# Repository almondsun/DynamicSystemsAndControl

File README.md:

# Sistemas Dinámicos y Control

Coursework and final Buck-converter project at Universidad Nacional de Colombia, Sede Manizales.

## Final project

- [Project documentation](project/README.md)
- [Four IEEE deliverable reports](project/reports/final/)
- [Hardware appendix: 3D views, schematics and wiring](project/pcb/release/hardware-appendix.pdf)
- [PCB design and build instructions](project/pcb/README.md)
- [STM32 firmware](project/firmware/README.md)
- [Requirements audit and next steps](project/pcb/docs/requirements-audit.md)
- [Buck SMD/JLCPCB audit: inventory, passive requirements and open issues](project/pcb/audit/README.md)
- [Team review package](project/pcb/release/buck-team-review.zip)

The design targets 12 V input, 6 V nominal output and 10 kHz PWM. Reports distinguish numerical simulations and CAD checks from experimental evidence. Component qualification, prototype assembly and physical testing remain pending; PCB fabrication is on hold.

## Repository contents

- `classroom/`: assignment and course reference material.
- `simulations/`: MATLAB and Simulink coursework.
- `project/`: final-project sources, reports, compact numerical results, PCB and firmware.
- `tools/` and `docs/`: validation helpers and MATLAB setup documentation.

Local downloaded toolchains, full raw validation runs and caches under `artifacts/` are excluded from Git. Follow the project documentation for build dependencies and reproducibility limits. Course materials and third-party assets retain their respective rights; KiCad model licensing is included in `project/pcb/models/`.

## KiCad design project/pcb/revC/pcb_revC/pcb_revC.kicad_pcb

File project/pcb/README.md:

# Buck: PCB y controlador STM32 — revisión A

**Paquete de ingeniería para revisión. Fabricación retenida hasta completar
la calificación de componentes y el prototipo soldado.** No se ha comprado,
fabricado, ensamblado ni probado físicamente esta tarjeta.

El diseño original conserva 12 V, 660 µH, 20 µF, 6 Ω y PWM de 10 kHz del
proyecto de Sistemas Dinámicos y Control. Emplea dos inductores de 330 µH en
serie, IR2110, MOSFET IRFZ44N, rectificación 1N5822 y una Blue Pill externa.
El controlador PI conserva la interfaz existente `buck_update` en voltios y
la salida invertida **d′ = 1 − d**. La protección por corriente y tensión
es independiente del programa del STM32.

## Archivos para compartir con el equipo

- [Auditoría SMD/JLCPCB e índice de documentación actual](audit/README.md): inventario de 57 referencias, requisitos calculados de los 35 pasivos y selección comercial pendiente.
- [Bloqueos antes de cambiar el circuito o fabricar](audit/open_issues.md) y [comportamiento esperado y pruebas](audit/expected_behavior.md). Los resultados de revisión A que siguen abajo son históricos; no constituyen una validación de los nuevos candidatos SMD.
- [Organización de documentos y bibliotecas descargadas](audit/organization_by_type.md) y [uso del organizador local](docs/vendor-assets-organizer.md). Las descargas originales y bibliotecas comerciales permanecen fuera de Git.

- [Anexo visual de hardware](release/hardware-appendix.pdf): 3D, plano, conexiones y esquemas completos.
- [Cuatro informes IEEE actualizados](../reports/final/) y [auditoría de requisitos](docs/requirements-audit.md).
- [Vista 3D isométrica](release/report-assets/pcb-3d.png) y [superior](release/report-assets/pcb-top.png). Son vistas CAD; geometría de inductores y referencias de capacitores pendientes de calificación.
- [Paquete ZIP completo](release/buck-team-review.zip) y [resumen para el equipo](TEAM_OVERVIEW.md).
- [Esquemático PDF](release/schematic.pdf) y [proyecto KiCad](buck.kicad_pro).
- [Vista frontal](release/board-front.png), [vista posterior](release/board-back.png)
  y [plano de montaje](release/assembly.pdf).
- [BOM de la placa](bom.csv) y [lista de compra con reservas](purchasing.csv).
- [Presupuesto y proveedores](docs/purchasing.md).
- [Montaje, conexiones y ensayos](docs/assembly-and-tests.md).
- [Firmware y programación](../firmware/README.md).
- [Resultados de validación y límites](VALIDATION.md).
- [Archivos de fabricación para revisión](release/fabrication-review/).

Los Gerbers son una exportación de revisión, **no una autorización para
encargar placas**. La geometría de L1/L2 es provisional: cuerpo máximo
25 mm, separación de terminales 10 mm, agujero 1.3 mm. Una bobina comercial
rotulada «330 µH, 5 A» no acredita esta geometría ni su corriente de saturación.
También deben cerrarse referencias exactas de los capacitores antes del pedido.

## Construcción y reproducción

Para actualizar las ilustraciones con las herramientas locales: `bash project/pcb/tools/render_review.sh`.
Esto adjunta modelos locales al PCB existente; no regenera ni enruta la placa. Tras ejecutar `generate.py`, repetir la importación de ruta y luego este paso de modelos. Ejecutar `export_review.sh` para comprobar ERC/DRC/paridad.
Los modelos estándar conservan su licencia oficial en `models/LICENSE-KiCad.md`; `models/manifest.json` registra procedencia y SHA-256. Las envolventes de inductores se generan en `prepare_3d.py` y no son modelos de fabricante.

Los informes se reconstruyen con `project/python/build_reports.py` y los resultados completos guardados, según el README del proyecto. La fuente del anexo es `docs/hardware-appendix.tex`; compilar desde `release/` para resolver los PDF y figuras incluidos. Los CSV compactos del ZIP permiten revisar resultados y ejecutar pruebas; regenerar las gráficas de rizado requiere las ondas completas de la ejecución original.

KiCad 10.0.6, bibliotecas estándar de KiCad y Python `pcbnew`; GCC ARM para
STM32. Las bibliotecas propias están dentro de esta carpeta. No se necesita
una licencia comercial de CAD. El STM32 y su programador no están integrados
en la placa, por lo que pueden reemplazarse sin rehacerla.

`tools/design.py` contiene la conectividad, numeración de pines y colocación.
`tools/generate.py` genera los archivos editables y el DSN. **Regenerar reemplaza
los archivos CAD generados**: conservar por separado cualquier revisión manual.
`tools/finish_board.py` importa la sesión de Freerouting y añade el plano GND.
Las comprobaciones finales y sus comandos están en `VALIDATION.md`.

El circuito de `simulation/` es una estimación con pérdidas y el código real
del controlador; no reemplaza el modelo Simulink ni los resultados originales.
Los informes de las entregas 2 y 4 siguen pendientes de evidencia experimental.

## Especificación de fabricación propuesta

99 × 99 mm; 2 capas; FR-4 de 1.6 mm; cobre de 1 oz; máscara verde;
acabado HASL sin plomo o estándar según el presupuesto; cinco placas desnudas;
sin montaje, stencil ni opciones premium. Señales de 0.30 mm, conexiones de
potencia de 0.60 mm y plano GND posterior; separación de ruteo 0.25 mm;
vías de 1.20/0.60 mm. Verificar calentamiento y caídas de tensión en banco:
estas dimensiones no sustituyen la validación térmica.
La salida GND de baja corriente de U6 incluye un escape local de 0.36 mm.
Su salida ISENSE incluye dos segmentos locales de 0.225 mm entre pads SOT23.

No hay orificios para chasis. Sujetar la placa por sus bordes con un soporte
aislante; los inductores pesados necesitan fijación aislante que no obstruya
la refrigeración. Nunca apoyar la cara inferior sobre una superficie metálica.

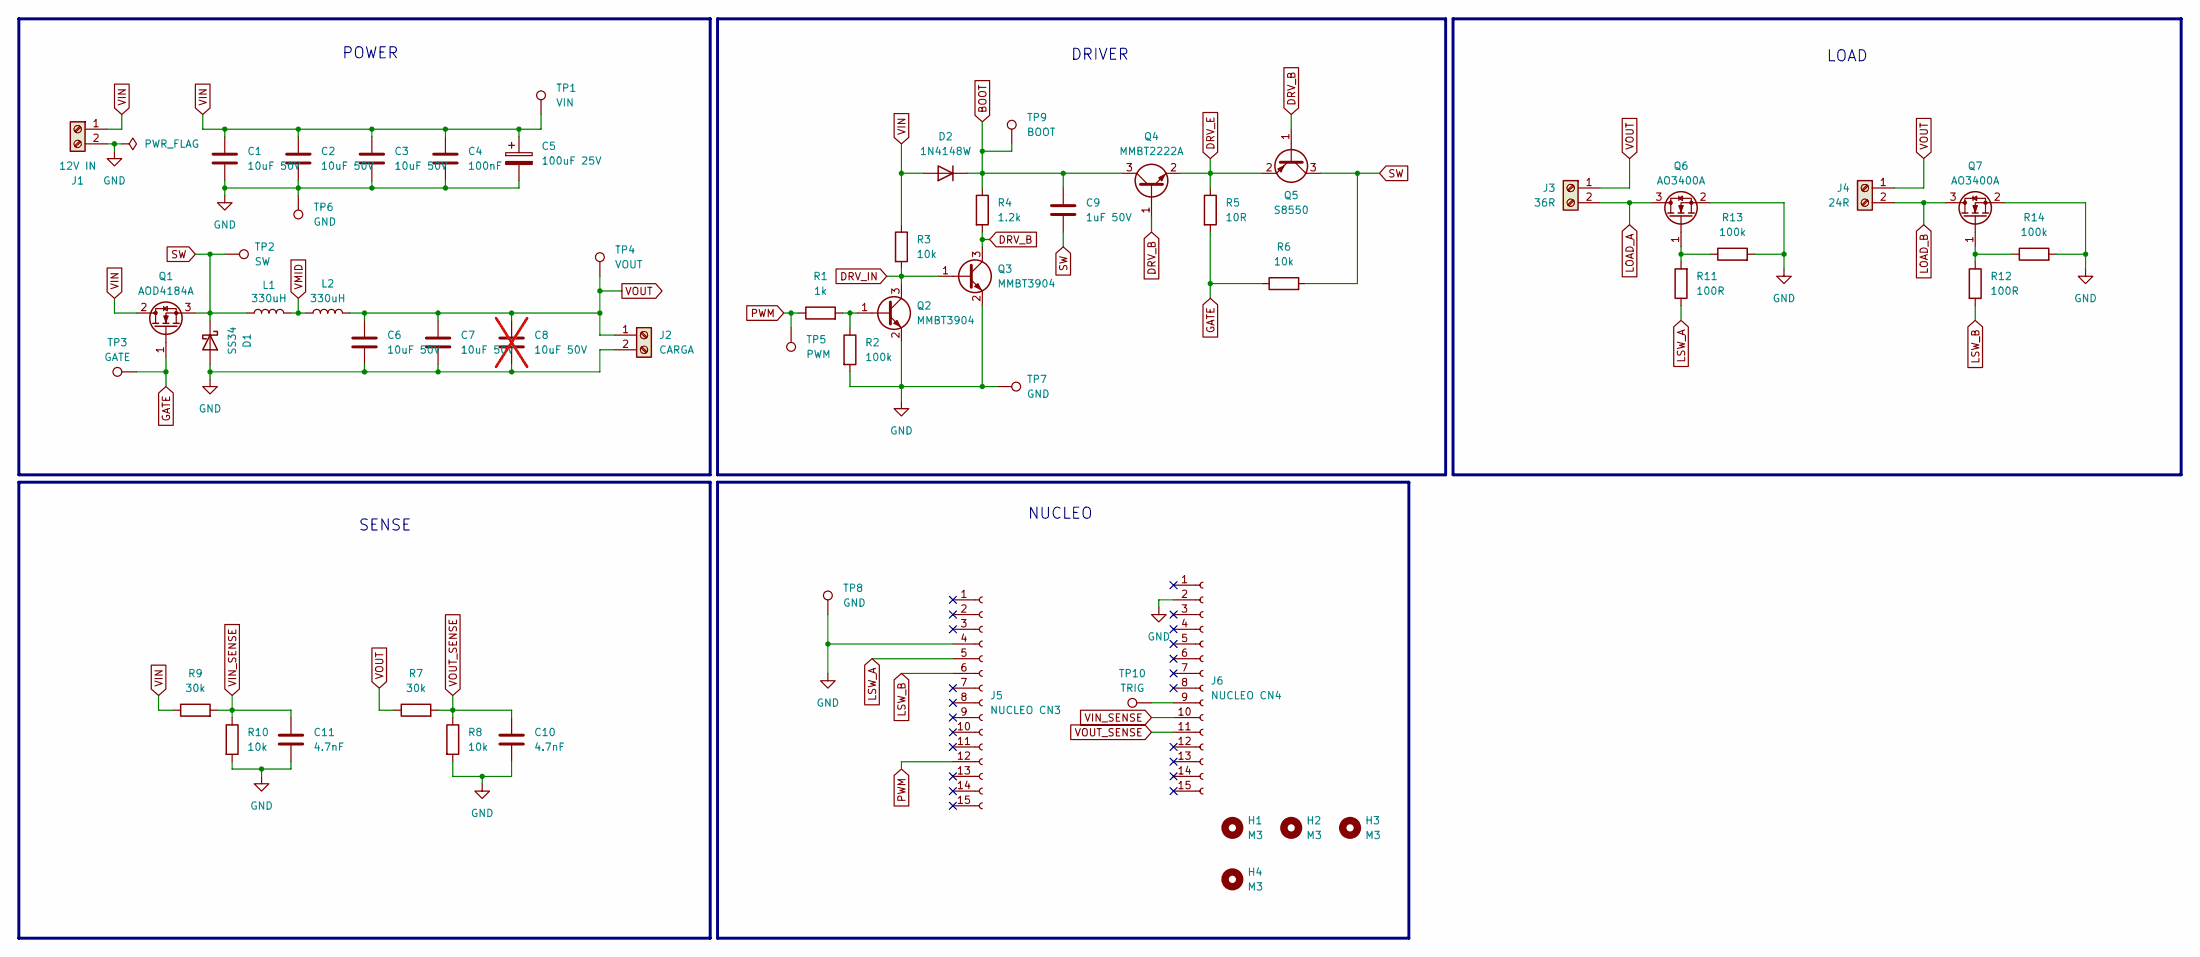
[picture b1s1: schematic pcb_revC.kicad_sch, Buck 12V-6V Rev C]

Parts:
C1, C2, C3, C6, C7: 10uF 50V; C_1206_3216Metric; LCSC C13585
C4: 100nF; C_0603_1608Metric; LCSC C14663
C5: 100uF 25V; CP_Radial_D6.3mm_P2.50mm
C8: 10uF 50V; C_1206_3216Metric; LCSC C13585; not fitted
C9: 1uF 50V; C_0805_2012Metric; LCSC C28323
C10, C11: 4.7nF; C_0603_1608Metric; LCSC C53987
D1: SS34; D_SMA; LCSC C8678
D2: 1N4148W; D_SOD-123; LCSC C81598
H1, H2, H3, H4: M3; MountingHole_3.2mm_M3
J1: 12V IN; TerminalBlock_Phoenix_MKDS-1,5-2_1x02_P5.00mm_Horizontal
J2: CARGA; TerminalBlock_Phoenix_MKDS-1,5-2_1x02_P5.00mm_Horizontal
J3: 36R; TerminalBlock_Phoenix_MKDS-1,5-2_1x02_P5.00mm_Horizontal
J4: 24R; TerminalBlock_Phoenix_MKDS-1,5-2_1x02_P5.00mm_Horizontal
J5: NUCLEO CN3; PinSocket_1x15_P2.54mm_Vertical
J6: NUCLEO CN4; PinSocket_1x15_P2.54mm_Vertical
L1, L2: 330uH; L_Bourns_SRR1280; LCSC C2041412
Q1: AOD4184A; TO-252-2; LCSC C99124
Q2, Q3: MMBT3904; SOT-23; LCSC C20526
Q4: MMBT2222A; SOT-23; LCSC C8512
Q5: S8550; SOT-23; LCSC C105432
Q6, Q7: AO3400A; SOT-23; LCSC C20917
R1: 1k; R_0603_1608Metric; LCSC C21190
R2, R13, R14: 100k; R_0603_1608Metric; LCSC C25803
R3, R6, R8, R10: 10k; R_0603_1608Metric; LCSC C25804
R4: 1.2k; R_0805_2012Metric; LCSC C17379
R5: 10R; R_0603_1608Metric; LCSC C22859
R7, R9: 30k; R_0603_1608Metric; LCSC C22984
R11, R12: 100R; R_0603_1608Metric; LCSC C22775
TP1: VIN; TestPoint_THTPad_D2.0mm_Drill1.0mm
TP2: SW; TestPoint_THTPad_D2.0mm_Drill1.0mm
TP3: GATE; TestPoint_THTPad_D2.0mm_Drill1.0mm
TP4: VOUT; TestPoint_THTPad_D2.0mm_Drill1.0mm
TP5: PWM; TestPoint_THTPad_D2.0mm_Drill1.0mm
TP6, TP7, TP8: GND; TestPoint_THTPad_D2.0mm_Drill1.0mm
TP9: BOOT; TestPoint_THTPad_D2.0mm_Drill1.0mm
TP10: TRIG; TestPoint_THTPad_D2.0mm_Drill1.0mm

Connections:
BOOT: C9.1, D2.1 (K), Q4.3 (C), R4.1, TP9.1 (1_1)
DRV_B: Q3.3 (C), Q4.1 (B), Q5.1 (B), R4.2
DRV_E: Q4.2 (E), Q5.2 (E), R5.1
DRV_IN: Q2.3 (C), Q3.1 (B), R3.2
GATE: Q1.1 (G), R5.2, R6.1, TP3.1 (1_1)
GND: C1.2, C2.2, C3.2, C4.2, C5.2, C6.2, C7.2, C8.2, C10.2, C11.2, D1.2 (A), J1.2, J2.2, J5.4, J6.2, Q2.2 (E), Q3.2 (E), Q6.2 (S), Q7.2 (S), R2.2, R8.2, R10.2, R13.2, R14.2, TP6.1 (1_1), TP7.1 (1_1), TP8.1 (1_1)
LOAD_A: J3.2, Q6.3 (D)
LOAD_B: J4.2, Q7.3 (D)
LSW_A: J5.5, R11.1
LSW_B: J5.6, R12.2
unnamed: J6.9, TP10.1 (1_1)
unnamed: Q2.1 (B), R1.2, R2.1
unnamed: Q6.1 (G), R11.2, R13.1
unnamed: Q7.1 (G), R12.1, R14.1
PWM: J5.12, R1.1, TP5.1 (1_1)
SW: C9.2, D1.1 (K), L1.2, Q1.3 (S), Q5.3 (C), R6.2, TP2.1 (1_1)
VIN: C1.1, C2.1, C3.1, C4.1, C5.1, D2.2 (A), J1.1, Q1.2 (D), R3.1, R9.1, TP1.1 (1_1)
VIN_SENSE: C11.1, J6.10, R9.2, R10.1
VMID: L1.1, L2.1
VOUT: C6.1, C7.1, C8.1, J2.1, J3.1, J4.1, L2.2, R7.1, TP4.1 (1_1)
VOUT_SENSE: C10.1, J6.11, R7.2, R8.1

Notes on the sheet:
DRIVER
POWER
SENSE
NUCLEO
LOAD

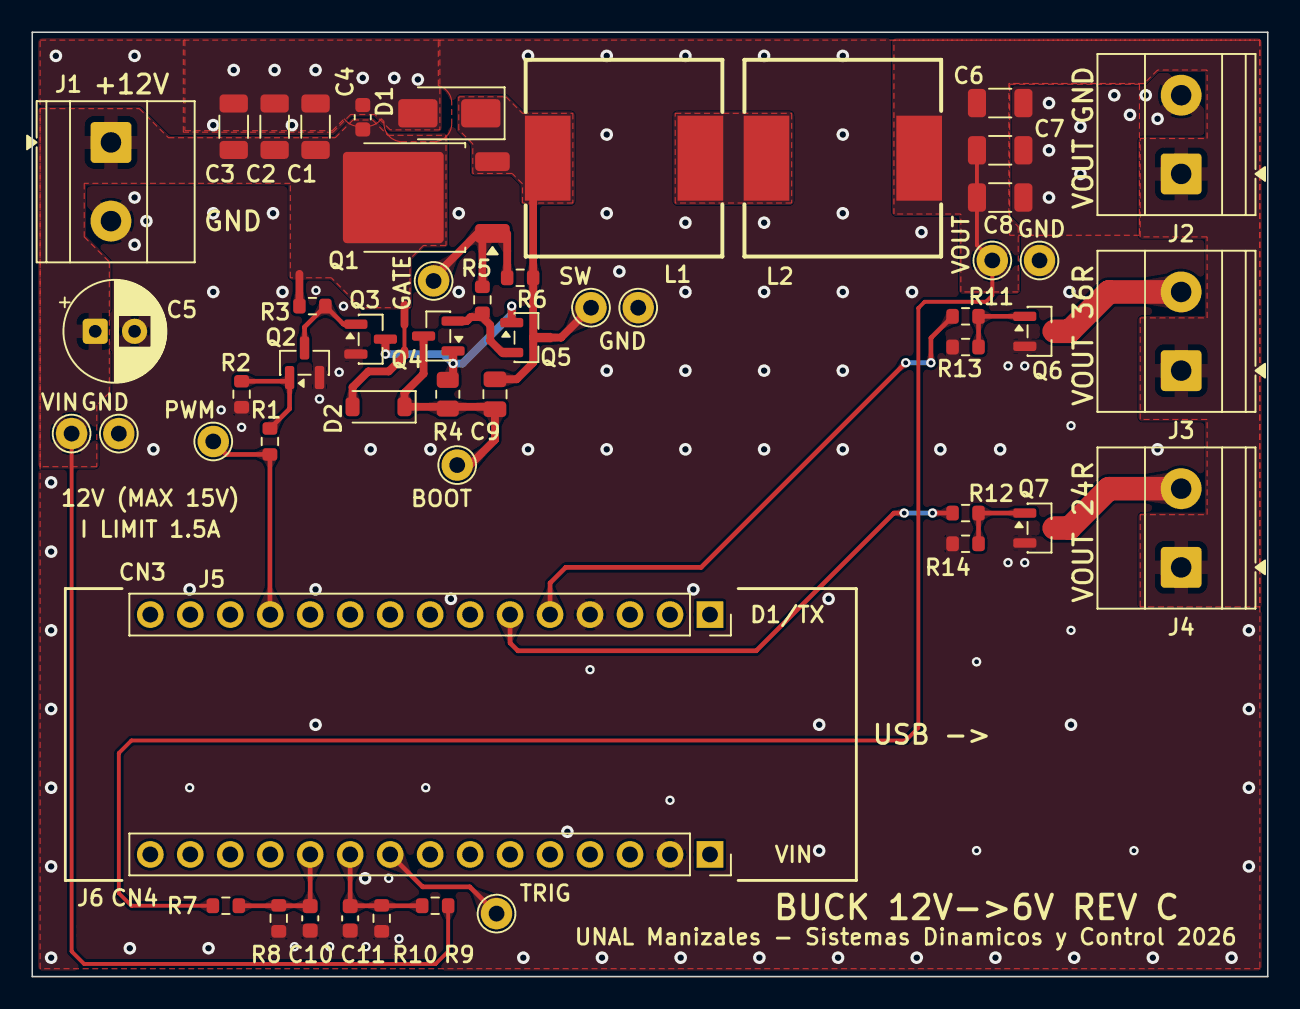
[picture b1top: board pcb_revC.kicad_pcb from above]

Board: 2 copper layers, 78.5 x 60.0 mm, 52 parts (0 on the bottom side), 21 nets.

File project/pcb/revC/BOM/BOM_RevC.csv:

Designator,Value,Package,LCSC,Library,Qty_per_board,Source,Notes
"L1,L2",SRR1280-331K 330uH 1.1A Isat1.4A DCR0.6R,SMD 12.5x12.5mm,C2041412,Extended,2,JLCPCB (reservados en My Parts Lib),En serie = 660uH; usar stock reservado
Q1,AOD4184A 40V 7mOhm,TO-252,C99124,Extended,1,JLCPCB,G=1 D=2/pestana S=3 - verificar datasheet
D1,SS34 40V 3A,SMA,C8678,Basic,1,JLCPCB,Catodo a SW
"C1,C2,C3,C6,C7",10uF 50V X5R,1206,C13585,Basic,5,JLCPCB,
C8,10uF 50V X5R,1206,C13585,Basic,0,JLCPCB,DNP - posicion de reserva
C4,100nF 50V X7R,0603,C14663,Basic,1,JLCPCB,Junto al drenador de Q1
C9,1uF 50V X7R,0805,C28323,Basic,1,JLCPCB,Bootstrap BOOT-SW
"C10,C11",4.7nF 50V X7R,0603,C53987,Basic,2,JLCPCB,Filtro ADC
"Q2,Q3",MMBT3904,SOT-23,C20526,Basic,2,JLCPCB,
Q4,MMBT2222A,SOT-23,C8512,Basic,1,JLCPCB,NPN del totem
Q5,S8550,SOT-23,C105432,Basic,1,JLCPCB,PNP del totem
"Q6,Q7",AO3400A,SOT-23,C20917,Basic,2,JLCPCB,Conmutacion de carga
D2,1N4148W,SOD-123,C81598,Basic,1,JLCPCB,Diodo de bootstrap
R1,1k 1%,0603,C21190,Basic,1,JLCPCB,
"R2,R13,R14",100k 1%,0603,C25803,Basic,3,JLCPCB,
"R3,R6,R8,R10",10k 1%,0603,C25804,Basic,4,JLCPCB,
R4,1.2k 1%,0805,C17379,Basic,1,JLCPCB,~44 mW promedio
R5,10R 1%,0603,C22859,Basic,1,JLCPCB,Resistencia de compuerta
"R7,R9",30k 1%,0603,C22984,Basic,2,JLCPCB,Divisores x0.25
"R11,R12",100R 1%,0603,C22775,Basic,2,JLCPCB,Compuerta de Q6/Q7
"J1,J2,J3,J4",Bornera 2P paso 5.0mm (KF301-5.0-2P),THT,,,4,Local,Paso 5.0 mm (huella Phoenix MKDS 5.00 mm) - no 5.08
"J5,J6",Header hembra 1x15 2.54mm,THT,,,2,Local,NUCLEO-L432KC CN3/CN4
C5,Electrolitico 100uF 25V o 35V radial 6.3mm paso 2.5mm 105C bajo ESR,THT,,,1,Local,Montar (soldar a mano). Rizado >= 0.3 A a 100 kHz. + = pad cuadrado (VIN)
"TP1-TP10",Test point pad 2.0mm / taladro 1.0mm,THT pad,,,10,Local,Pines macho 2.54 mm opcionales (VIN SW GATE VOUT PWM GND x3 BOOT TRIG)
"H1-H4",Agujero M3,NPTH 3.2mm,,,0,—,ELIMINADOS 2026-11-03 (sin agujeros M3; excluidos de la placa en el esquematico)
RCARGA_BASE,3.6R 10W x2 en serie (7.2R),Fuera de placa,,,2,Local,A J2
RCARGA_A,36R 5W,Fuera de placa,,,1,Local,A J3
RCARGA_B,24R 5W,Fuera de placa,,,1,Local,A J4

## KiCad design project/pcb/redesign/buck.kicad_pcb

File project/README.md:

# Proyecto final: convertidor Buck

Proyecto basado en `classroom/Descripcion Proyecto Buck.pdf`. Están desarrolladas
las entregas de simulación 1 y 3. Las entregas 2 y 4 incluyen metodología y
herramientas de análisis, pero requieren construir el convertidor y obtener
mediciones reales; no se presentan datos inventados.

## Documentos y modelo

La selección SMD para JLCPCB se documenta en la [auditoría de componentes del Buck](pcb/audit/README.md): inventario, requisitos eléctricos y térmicos de los 35 pasivos, candidatos comerciales y bloqueos. Es una revisión documental posterior al diseño original; no aprueba componentes ni fabricación y no recalifica los resultados históricos para SMD.

| Entrega | Archivo | Estado |
|---|---|---|
| 1. Modelo y simulación | [Informe PDF](reports/final/entrega_1.pdf) · [Fuente LaTeX](reports/final/entrega_1.tex) | Simulación completada |
| 2. Lazo abierto experimental | [Documento PDF](reports/final/entrega_2.pdf) · [Fuente LaTeX](reports/final/entrega_2.tex) | Ensayos físicos pendientes |
| 3. Diseño del PI | [Informe PDF](reports/final/entrega_3.pdf) · [Fuente LaTeX](reports/final/entrega_3.tex) | Simulación completada |
| 4. Controlador implementado | [Documento PDF](reports/final/entrega_4.pdf) · [Fuente LaTeX](reports/final/entrega_4.tex) | Integración y ensayos físicos pendientes |

- [Modelo Simulink](models/buck_control.slx): PI, saturación, anti-windup,
  driver inversor y planta promediada. Parámetros guardados en el workspace del modelo.
- [Circuito ngspice](circuit/buck.cir.in) y [descripción](circuit/README.md).
- [Implementación y protocolo de laboratorio](hardware/implementacion.md).
- [Núcleo C del controlador](hardware/buck_control.c): validado en computador;
  [adaptador STM32F103](firmware/README.md) compilable, con validación en computador;
  falta verificarlo en la tarjeta física.
- [PCB, lista de compra y protocolo de montaje](pcb/README.md): diseño KiCad
  de revisión; fabricación retenida hasta calificar componentes y prototipo.
- [Contrato de datos experimentales](data/README.md) y
  [analizador](python/analyze_experiment.py).
- [Registro de validación](VALIDATION.md).
- [Datos y evidencia numérica](results/README.md): CSV, MAT, JSON, netlists y logs.

## Parámetros y resultados

Vin=12 V, L=660 µH, C=20 µF, R=6 Ω, PWM=10 kHz. La figura del proyecto usa
660 µH; el valor 270 µH de `Ej_Buck.m` corresponde a otro ejemplo.

La entrada es **d′=1−d**. Aumentar d′ reduce la tensión. La planta incremental es

```text
Gd′(s) = −12 / (1.32e−8 s² + 1.10e−4 s + 1)
```

El PI actúa sobre el duty físico con Kp=0.0261655286 V⁻¹ y
Ki=78.4965859 (V·s)⁻¹; la salida lógica es d′=1−d. El diseño continuo tiene
102.07° de margen de fase y 4.83 ms de establecimiento nominal.

Los seis escenarios PWM/ngspice y los cuatro de Simulink pasan. En ngspice,
los cambios 6→7 V y 6→5 V se establecen en 4.95 ms (banda ±20 mV sobre medias
de periodo). Los cambios de R ±20% se establecen en 0.65 ms (banda ±0.12 V).
La diferencia por reducir el paso de ngspice a la mitad es 0.927 mV.

En lazo abierto, el circuito con pérdidas queda unos 0.30 V por debajo del
modelo ideal. El rizado es aproximadamente 0.28–0.29 V pico a pico. Los
semiconductores de ngspice son genéricos y DCR/ESR son supuestos explícitos;
estos resultados no certifican un montaje físico.

## Abrir y simular en MATLAB

Desde la raíz del repositorio:

```matlab
open_system('project/models/buck_control.slx')
in = Simulink.SimulationInput('buck_control');
in = in.setVariable('RefFinal',5,'Workspace','buck_control');
in = in.setVariable('RFinal',6,'Workspace','buck_control');
out = sim(in);
plot(out.buck_signals.Time, out.buck_signals.Data(:,1))
xlabel('Tiempo (s)'); ylabel('Tensión de salida (V)'); grid on
```

Para los otros escenarios elegir (RefFinal,RFinal): (7,6), (6,7.2), (6,4.8).
Las cuatro columnas registradas son tensión, corriente, d′ y referencia.
Condición inicial: 6 V y 1 A; evento a 10 ms; tiempo final 30 ms; ode45,
RelTol=1e-8, AbsTol=1e-10, MaxStep=10 µs. No se borra el workspace del usuario.

## Reproducir todo

Requisitos: MATLAB/Simulink/Control System Toolbox R2026a, ngspice 44.2,
Python 3.14 con [requirements.txt](python/requirements.txt), GCC y Tectonic
0.15.0 para los PDF LaTeX. No se necesitan Simscape, Simulink Test ni
Simulink Control Design. La reconstrucción estructural opcional utiliza el
toolkit oficial SATK, mediante `build_buck_model.m`; el modelo ya entregado
puede simularse sin SATK.

Con las herramientas disponibles en esta máquina:

```bash
BUCK_MATLAB=/home/mitin/MATLAB/R2026a/bin/matlab \
BUCK_PYTHON="$PWD/artifacts/buck-tools/venv/bin/python" \
BUCK_NGSPICE="$PWD/artifacts/buck-tools/ngspice/usr/bin/ngspice" \
bash project/run_project.sh
```

En otra máquina, instalar las dependencias de Python en un entorno virtual y
usar rutas propias o los ejecutables `matlab`, `python` y `ngspice` del PATH.
La distribución local de ngspice está extraída en `artifacts/buck-tools/`, sin
cambiar paquetes del sistema. Sus bibliotecas se seleccionan sólo para el
subproceso ngspice; no se cambian las bibliotecas de MATLAB.

El ejecutor crea una carpeta nueva bajo `artifacts/`, guarda CSV, MAT, JSON,
netlists por caso, formas de onda, logs, pruebas y PDF. Si se pasa una carpeta
ya existente, se detiene para evitar sobrescrituras. Ejemplo:
`bash project/run_project.sh artifacts/mi-nueva-ejecucion`.

## Completar las entregas físicas

Seguir `hardware/implementacion.md`: medir R/L/C y pérdidas; construir y
verificar la etapa de potencia y driver; elegir tarjeta; integrar ADC/PWM;
capturar dos ensayos de lazo abierto y cuatro de lazo cerrado con repeticiones.
Después, incorporar las mediciones y conclusiones a los documentos 2 y 4.
El analizador no convierte nominales de simulación en parámetros medidos.

## Reconstruir sólo los informes

Los cuatro PDF usan IEEEtran, ecuaciones LaTeX numeradas, CircuitikZ y gráficas
vectoriales PGFPlots. Las fuentes editables principales son `entrega_N.tex`;
los `.md` son compañeros con delimitadores matemáticos. Los autores aparecen
tanto en el documento como en los metadatos PDF. Las entregas 2 y 4 siguen
identificadas como metodologías con resultados experimentales pendientes.

El compilador local está en `artifacts/buck-tools/tectonic/tectonic`. Se puede
seleccionar otro con `BUCK_TECTONIC` o `--tectonic`. La primera compilación
necesita acceso a Internet para llenar la caché de paquetes de Tectonic.
El binario oficial utilizado es `tectonic-0.15.0-x86_64-unknown-linux-musl.tar.gz`,
de [la publicación 0.15.0](https://github.com/tectonic-typesetting/tectonic/releases/tag/tectonic%400.15.0).
SHA-256 del archivo descargado:
`dfb82876f2986862996e564fa507a9e576e0c1e3bee63c2c1bd677c2543e6407`.

```bash
artifacts/buck-tools/venv/bin/python -B project/python/build_reports.py \
  --matlab-results project/results/matlab \
  --analysis-results artifacts/buck-final-validation-02/simulation \
  --output artifacts/mis-informes-latex
```

La carpeta de salida debe ser nueva. Para reconstruir desde simulaciones se
requieren sus `waveform.txt`, además de JSON y CSV PWM, para obtener el detalle
instantáneo del rizado. Esto no vuelve a ejecutar MATLAB ni ngspice. Las fuentes
TeX entregadas también pueden compilarse directamente desde `reports/final/`:

```bash
../../../artifacts/buck-tools/tectonic/tectonic --keep-logs entrega_1.tex
```

El generador conserva los datos gráficos en `data/`, verifica coherencia de
parámetros y rechaza glifos faltantes, referencias indefinidas y desbordamientos.
La reducción de puntos retiene extremos por intervalo y extremos temporales;
las métricas proceden de resultados completos, sin recalcularlas sobre gráficos.
Validación de Python: `python -B -m unittest discover -s project/python -p 'test_*.py' -v`.

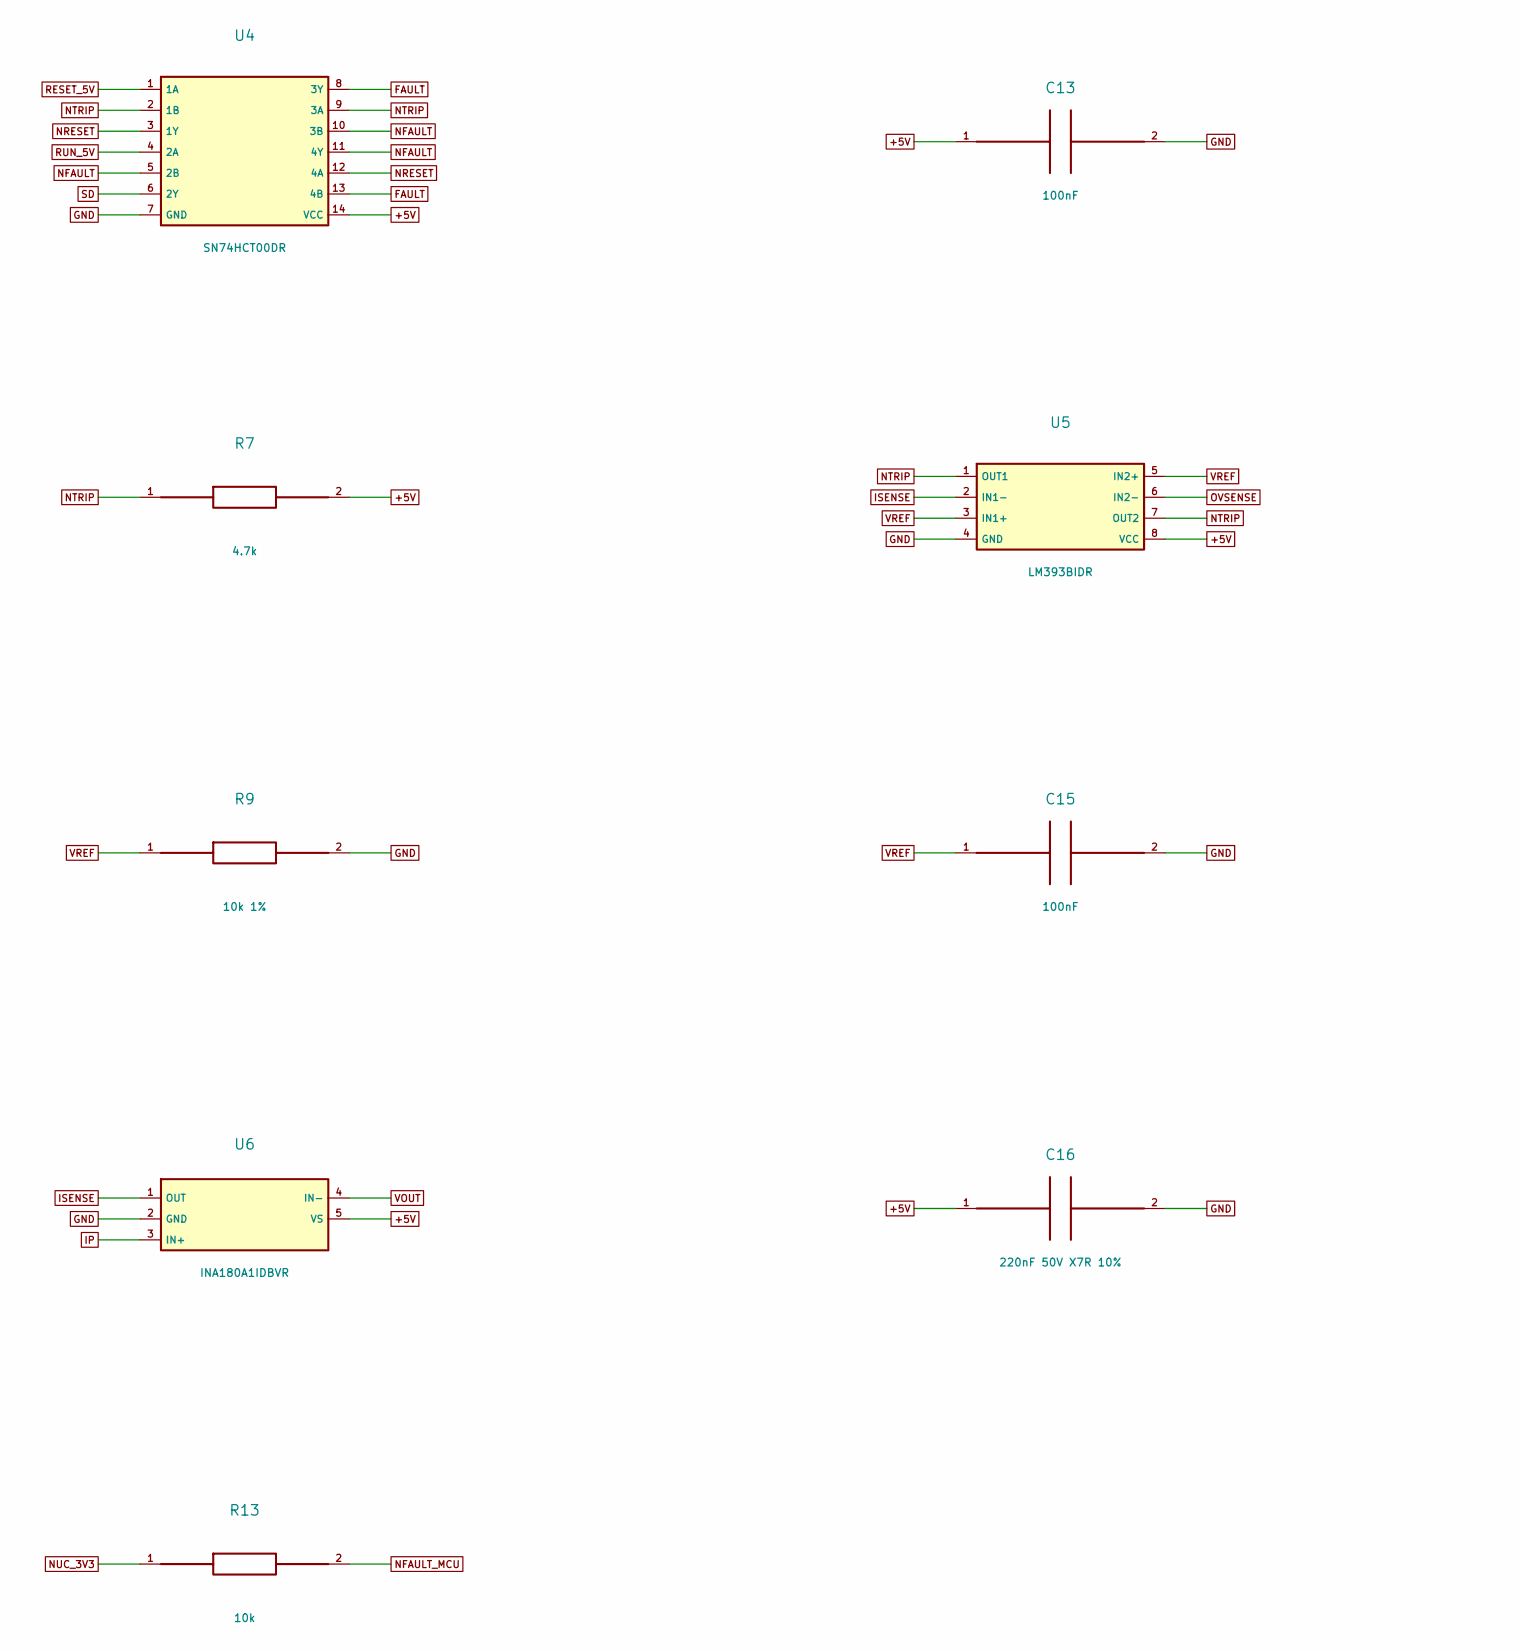
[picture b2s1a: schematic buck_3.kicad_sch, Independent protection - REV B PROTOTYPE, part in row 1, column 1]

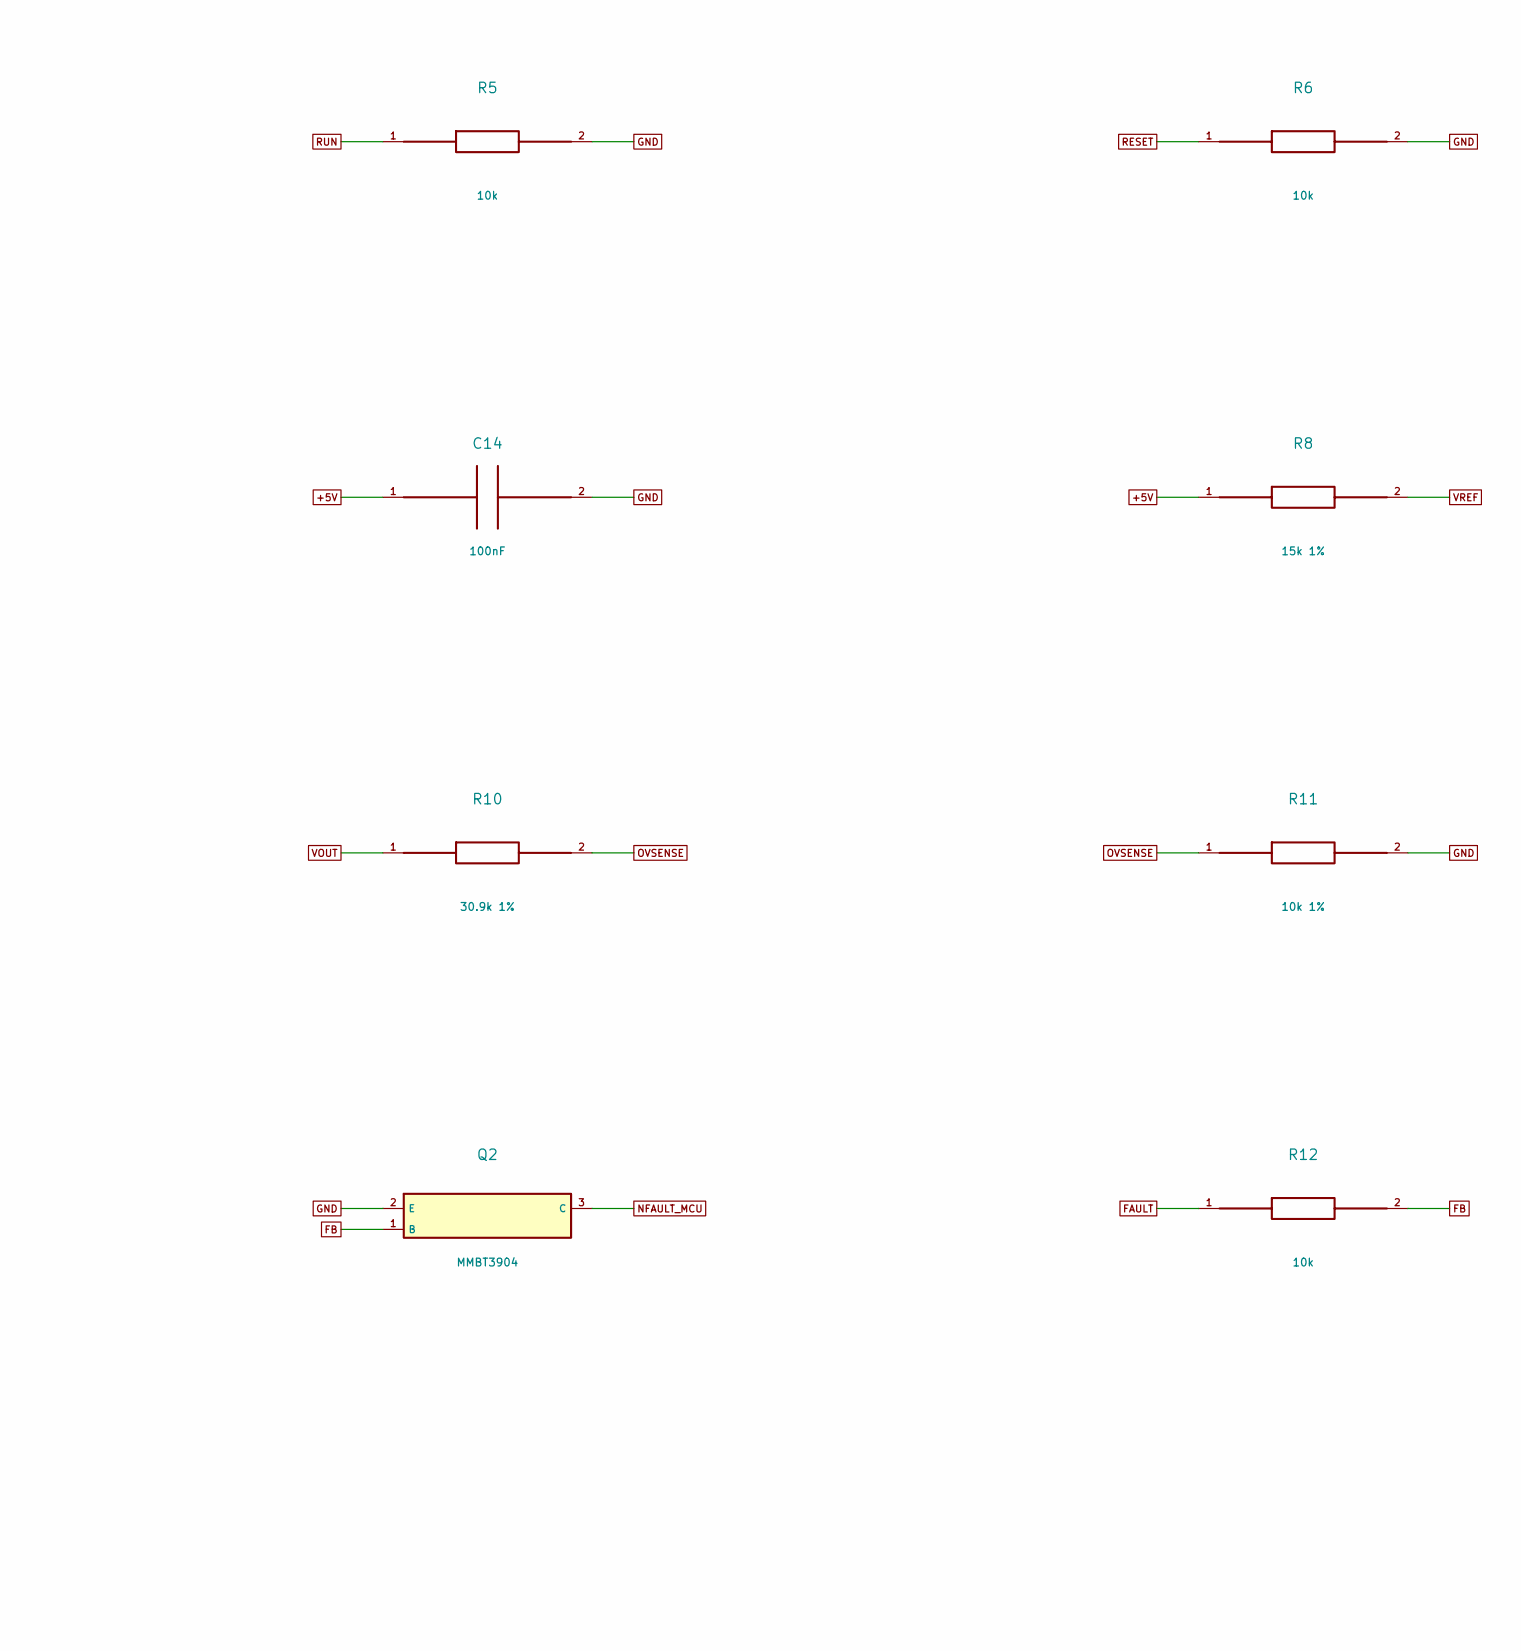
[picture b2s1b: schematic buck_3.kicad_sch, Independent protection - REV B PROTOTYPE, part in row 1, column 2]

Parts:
C13, C14, C15: 100nF; C_0603_1608Metric; MPN Yageo CC0603KRX7R9BB104; LCSC C14663
C16: 220nF 50V X7R 10%; C_0603_1608Metric; MPN CC0603KRX7R9BB224; LCSC C107083
Q2: MMBT3904; SOT-23; MPN MMBT3904; LCSC C20526
R5, R6, R12, R13: 10k; R_0603_1608Metric; MPN UNI-ROYAL 0603WAF1002T5E; LCSC C25804
R7: 4.7k; R_0603_1608Metric; MPN UNI-ROYAL 0603WAF4701T5E; LCSC C23162
R8: 15k 1%; R_0603_1608Metric; MPN UNI-ROYAL 0603WAF1502T5E; LCSC C22809
R9, R11: 10k 1%; R_0603_1608Metric; MPN UNI-ROYAL 0603WAF1002T5E; LCSC C25804
R10: 30.9k 1%; R_0603_1608Metric; MPN 0603WAF3092T5E; LCSC C23022
U4: SN74HCT00DR; TI_D0014A_SOIC-14; MPN SN74HCT00DR; LCSC C6764
U5: LM393BIDR; TI_D0008A_SOIC-8; MPN LM393BIDR; LCSC C2865059
U6: INA180A1IDBVR; TI_DBV0005A_SOT-23-5; MPN INA180A1IDBVR; LCSC C122228

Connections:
+5V: C13.1, C14.1, C16.1, R7.2, R8.1, U4.14 (VCC), U5.8 (VCC), U6.5 (VS); also elsewhere on the board
FAULT: R12.1, U4.8 (3Y), U4.13 (4B)
FB: Q2.1 (B), R12.2
GND: C13.2, C14.2, C15.2, C16.2, Q2.2 (E), R5.2, R6.2, R9.2, R11.2, U4.7 (GND), U5.4 (GND), U6.2 (GND); also elsewhere on the board
IP: U6.3 (IN+); also elsewhere on the board
ISENSE: U5.2 (IN1-), U6.1 (OUT); also elsewhere on the board
NFAULT: U4.5 (2B), U4.10 (3B), U4.11 (4Y)
NFAULT_MCU: Q2.3 (C), R13.2; also elsewhere on the board
NRESET: U4.3 (1Y), U4.12 (4A)
NTRIP: R7.1, U4.2 (1B), U4.9 (3A), U5.1 (OUT1), U5.7 (OUT2); also elsewhere on the board
NUC_3V3: R13.1; also elsewhere on the board
OVSENSE: R10.2, R11.1, U5.6 (IN2-)
RESET: R6.1; also elsewhere on the board
RESET_5V: U4.1 (1A); also elsewhere on the board
RUN: R5.1; also elsewhere on the board
RUN_5V: U4.4 (2A); also elsewhere on the board
SD: U4.6 (2Y); also elsewhere on the board
VOUT: R10.1, U6.4 (IN-); also elsewhere on the board
VREF: C15.1, R8.2, R9.1, U5.3 (IN1+), U5.5 (IN2+)

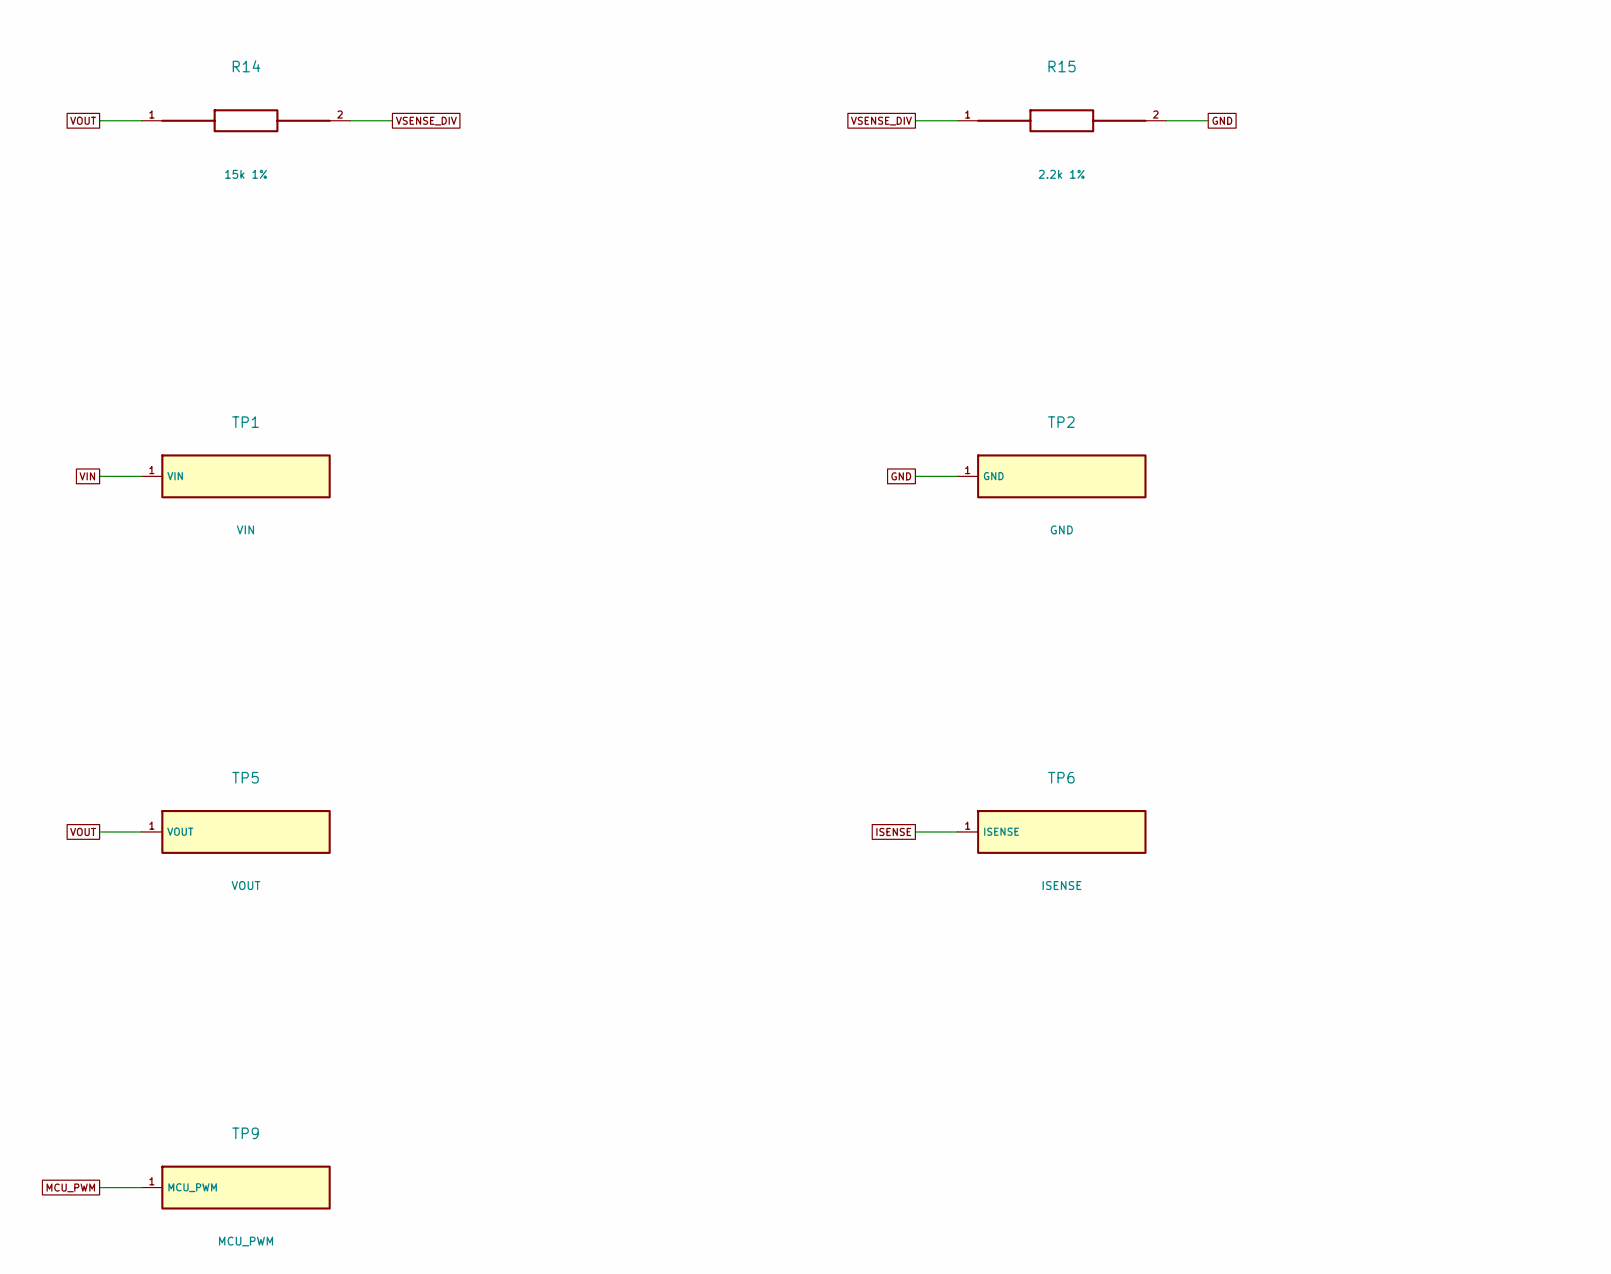
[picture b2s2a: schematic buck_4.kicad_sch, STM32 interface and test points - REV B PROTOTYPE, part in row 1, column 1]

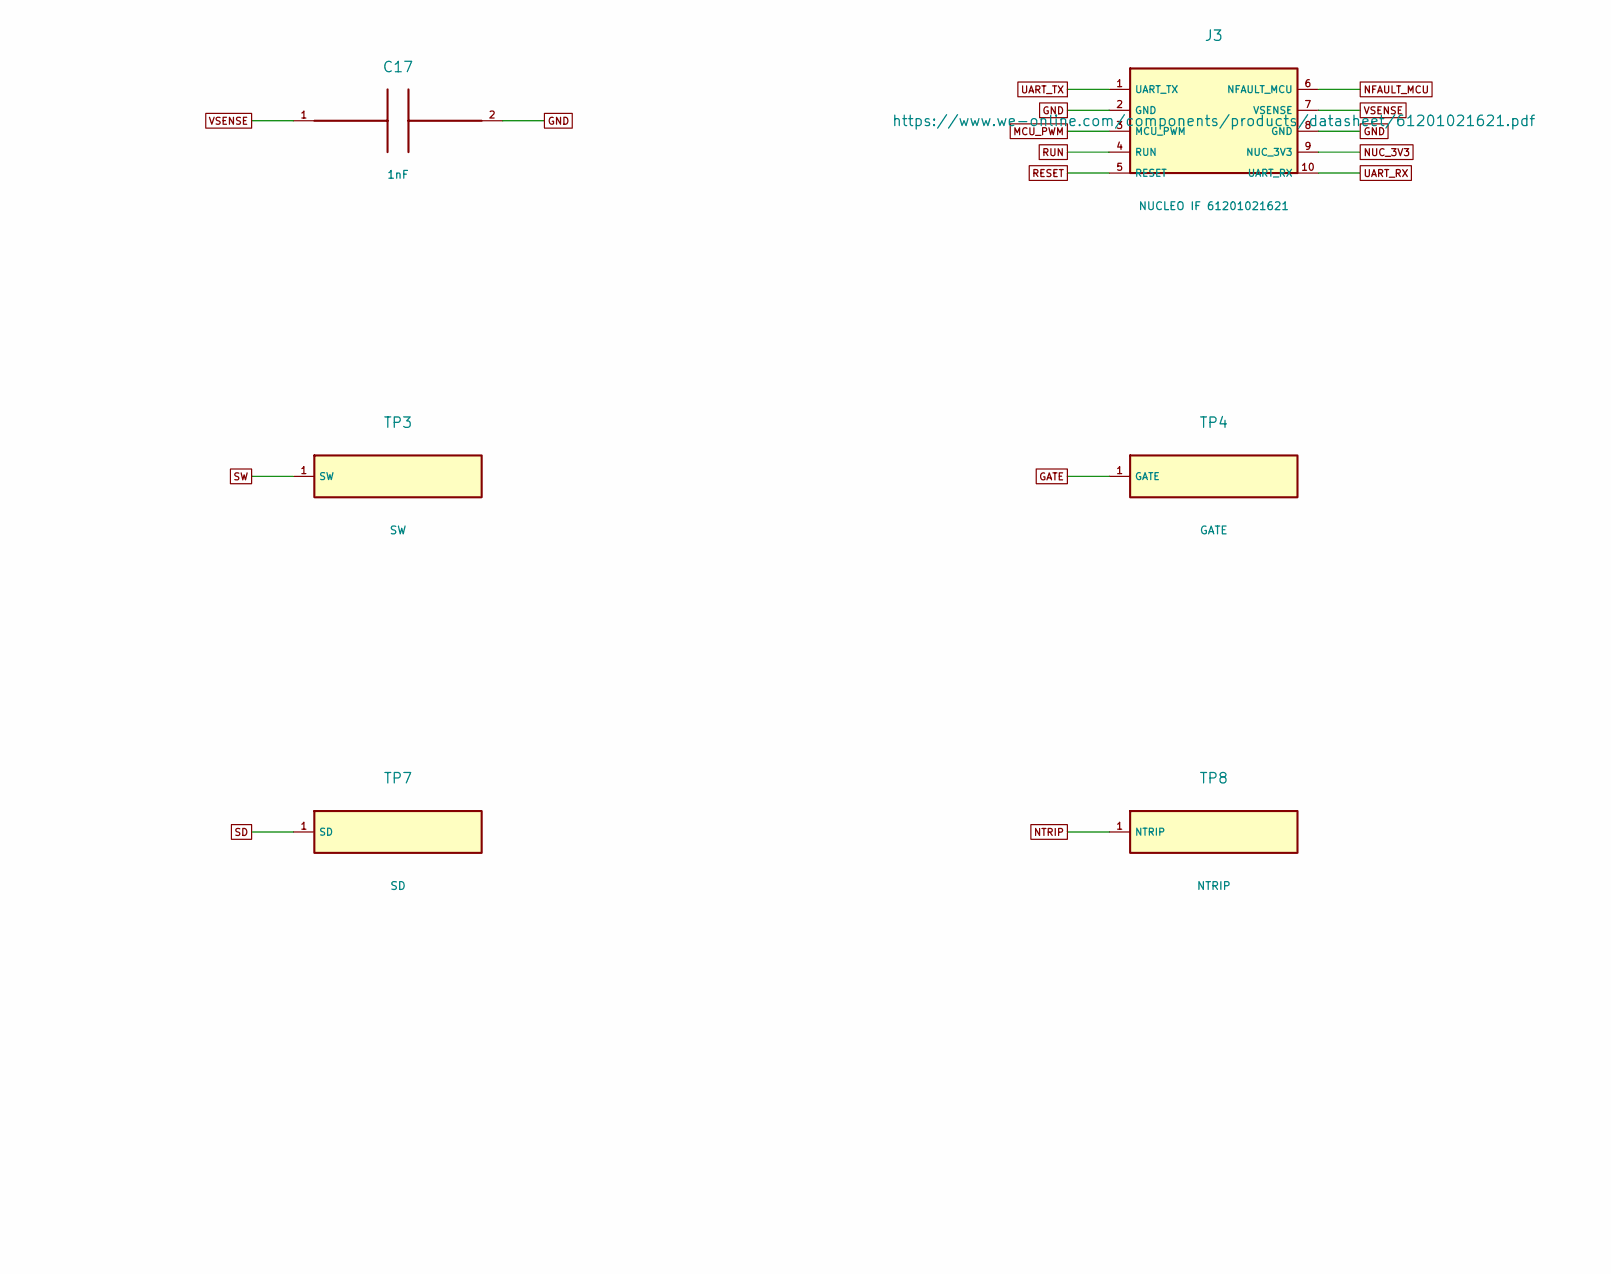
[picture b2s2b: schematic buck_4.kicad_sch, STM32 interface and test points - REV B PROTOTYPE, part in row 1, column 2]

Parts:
C17: 1nF; C_0603_1608Metric; MPN Fenghua 0603CG102J500NT; LCSC C1636
J3: NUCLEO IF 61201021621; Wurth_WR-BHD_61201021621_2x05_P2.54mm_Vertical; MPN 61201021621; LCSC C4355000
R14: 15k 1%; R_0603_1608Metric; MPN 0603WAF1502T5E; LCSC C22809
R15: 2.2k 1%; R_0603_1608Metric; MPN 0603WAF2201T5E; LCSC C4190
TP1: VIN; TestPoint_THTPad_D2.0mm_Drill1.0mm
TP2: GND; TestPoint_THTPad_D2.0mm_Drill1.0mm
TP3: SW; TestPoint_THTPad_D2.0mm_Drill1.0mm
TP4: GATE; TestPoint_THTPad_D2.0mm_Drill1.0mm
TP5: VOUT; TestPoint_THTPad_D2.0mm_Drill1.0mm
TP6: ISENSE; TestPoint_THTPad_D2.0mm_Drill1.0mm
TP7: SD; TestPoint_THTPad_D2.0mm_Drill1.0mm
TP8: NTRIP; TestPoint_THTPad_D2.0mm_Drill1.0mm
TP9: MCU_PWM; TestPoint_THTPad_D2.0mm_Drill1.0mm

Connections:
GATE: TP4.1 (GATE_1); also elsewhere on the board
GND: C17.2, J3.2 (GND), J3.8 (GND), R15.2, TP2.1 (GND_1); also elsewhere on the board
ISENSE: TP6.1 (ISENSE_1); also elsewhere on the board
MCU_PWM: J3.3 (MCU_PWM), TP9.1 (MCU_PWM_1); also elsewhere on the board
NFAULT_MCU: J3.6 (NFAULT_MCU); also elsewhere on the board
NTRIP: TP8.1 (NTRIP_1); also elsewhere on the board
NUC_3V3: J3.9 (NUC_3V3); also elsewhere on the board
RESET: J3.5 (RESET); also elsewhere on the board
RUN: J3.4 (RUN); also elsewhere on the board
SD: TP7.1 (SD_1); also elsewhere on the board
SW: TP3.1 (SW_1); also elsewhere on the board
UART_RX: J3.10 (UART_RX)
UART_TX: J3.1 (UART_TX)
VIN: TP1.1 (VIN_1); also elsewhere on the board
VOUT: R14.1, TP5.1 (VOUT_1); also elsewhere on the board
VSENSE: C17.1, J3.7 (VSENSE); also elsewhere on the board
VSENSE_DIV: R14.2, R15.1; also elsewhere on the board
